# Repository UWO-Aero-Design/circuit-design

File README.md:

# WE Aero Design Onboard Hardware

## Goal
The hardware soloution will contain sensors that allow the team to accurately determine the height and position of the aircraft at any given moment. Also, the system should allow for communication with the ground station through an onboard radio. Logging of in-flight data and accurate GPS information will be necessary. Finally, the system must be able to control 16 individual servos or DC motors.

## Design
Below are screenshots of the current revision of the schematic and board (created in Eagle).

### Schematic

### Board

## Features
#### Radio
[RFM95W](https://www.adafruit.com/product/3072)

#### IMU
[MPU9250](https://www.sparkfun.com/products/13762)

#### Evironment Sensing
[MPL3115A2](https://www.adafruit.com/product/1893)

#### GPS
[Adafruit Ultimate GPS Breakout](https://www.adafruit.com/product/746?gclid=CjwKCAjwscDpBRBnEiwAnQ0HQNEhq5xu14W7TX12W0gVZqHBnbDJNApMf9mEeb73NOOZy2kR0mpCVRoCgI8QAvD_BwE)

#### Battery Monitoring
[INA219](https://www.adafruit.com/product/904)

#### Servo Driver
[PCA9686](https://cdn-shop.adafruit.com/datasheets/PCA9685.pdf)

#### Power
[L7805 and L7806](https://www.mouser.ca/datasheet/2/389/l78m-974157.pdf)

## TODO
- [x] Select parts
- [x] Create schematic
- [x] Layout board
- [x] Route board
- [ ] Order board
- [ ] Test board

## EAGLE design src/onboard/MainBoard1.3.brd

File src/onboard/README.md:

# WE Aero Design Onboard Hardware

## Goal
The hardware soloution will contain sensors that allow the team to accurately determine the height and position of the aircraft at any given moment. Also, the system should allow for communication with the ground station through an onboard radio. Logging of in-flight data and accurate GPS information will be necessary. Finally, the system must be able to control 16 individual servos or DC motors.

## Design
Below are screenshots of the current revision of the schematic and board (created in Eagle).

### Schematic

### Board

## Features
#### Radio
[RFM95W](https://www.adafruit.com/product/3072)

#### IMU
[MPU9250](https://www.sparkfun.com/products/13762)

#### Evironment Sensing
[MPL3115A2](https://www.adafruit.com/product/1893)

#### GPS
[Adafruit Ultimate GPS Breakout](https://www.adafruit.com/product/746?gclid=CjwKCAjwscDpBRBnEiwAnQ0HQNEhq5xu14W7TX12W0gVZqHBnbDJNApMf9mEeb73NOOZy2kR0mpCVRoCgI8QAvD_BwE)

#### Servo Driver
[PCA9686](https://cdn-shop.adafruit.com/datasheets/PCA9685.pdf)

#### Power
[L7805 and L7806](https://www.mouser.ca/datasheet/2/389/l78m-974157.pdf)

## TODO
- [x] Select parts
- [x] Create schematic
- [x] Layout board
- [x] Route board
- [x] Order board
- [ ] Test board

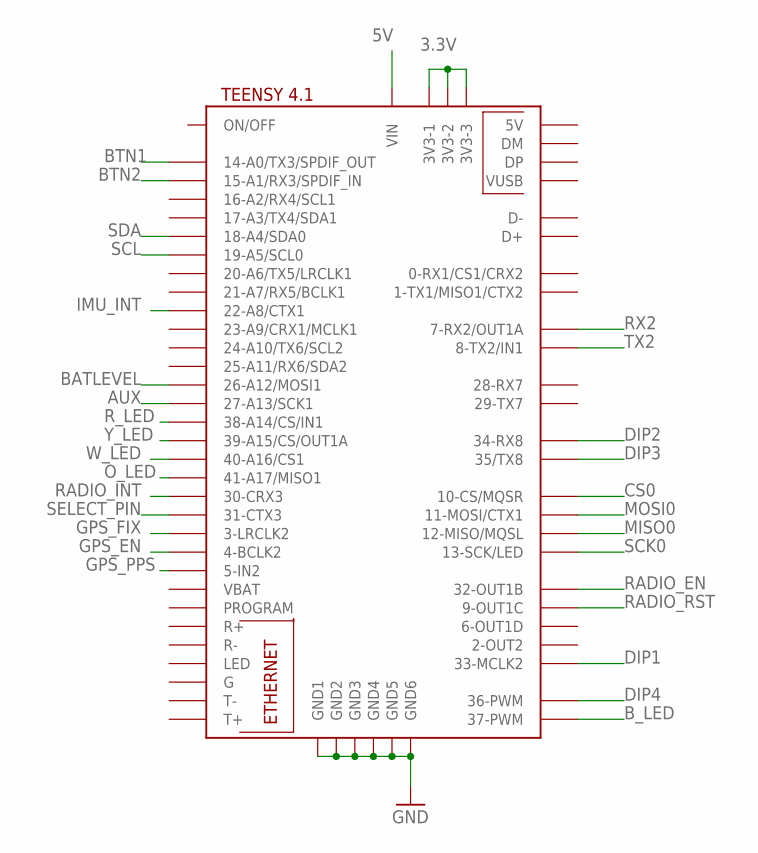
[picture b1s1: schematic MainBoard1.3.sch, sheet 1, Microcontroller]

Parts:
TEENSY4.1: TEENSY41

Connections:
3.3V: TEENSY4.1.3V3-1, TEENSY4.1.3V3-2, TEENSY4.1.3V3-3; also elsewhere on the board
5V: TEENSY4.1.VIN; also elsewhere on the board
AUX: TEENSY4.1.27-A13/SCK1; also elsewhere on the board
BATLEVEL: TEENSY4.1.26-A12/MOSI1; also elsewhere on the board
BTN1: TEENSY4.1.14-A0/TX3/SPDIF_OUT; also elsewhere on the board
BTN2: TEENSY4.1.15-A1/RX3/SPDIF_IN; also elsewhere on the board
B_LED: TEENSY4.1.37-PWM; also elsewhere on the board
CS0: TEENSY4.1.10-CS\MQSR (10-CS/MQSR); also elsewhere on the board
DIP1: TEENSY4.1.33-MCLK2; also elsewhere on the board
DIP2: TEENSY4.1.34-RX8; also elsewhere on the board
DIP3: TEENSY4.1.35-TX8 (35/TX8); also elsewhere on the board
DIP4: TEENSY4.1.36-PWM; also elsewhere on the board
GND: TEENSY4.1.GND1, TEENSY4.1.GND2, TEENSY4.1.GND3, TEENSY4.1.GND4, TEENSY4.1.GND5, TEENSY4.1.GND6; also elsewhere on the board
GPS_EN: TEENSY4.1.4-BCLK2; also elsewhere on the board
GPS_FIX: TEENSY4.1.3-LRCLK2; also elsewhere on the board
GPS_PPS: TEENSY4.1.5-IN2; also elsewhere on the board
IMU_INT: TEENSY4.1.22-A8/CTX1; also elsewhere on the board
MISO0: TEENSY4.1.12-MISO/MQSL; also elsewhere on the board
MOSI0: TEENSY4.1.11-MOSI/CTX1; also elsewhere on the board
O_LED: TEENSY4.1.41-A17/MISO1; also elsewhere on the board
RADIO_EN: TEENSY4.1.32-OUT1B; also elsewhere on the board
RADIO_INT: TEENSY4.1.30-CRX3; also elsewhere on the board
RADIO_RST: TEENSY4.1.9-OUT1C; also elsewhere on the board
RX2: TEENSY4.1.7-RX2/OUT1A; also elsewhere on the board
R_LED: TEENSY4.1.38-A14/CS/IN1; also elsewhere on the board
SCK0: TEENSY4.1.13-SCK/LED; also elsewhere on the board
SCL: TEENSY4.1.19-A5/SCL0; also elsewhere on the board
SDA: TEENSY4.1.18-A4/SDA0; also elsewhere on the board
SELECT_PIN: TEENSY4.1.31-CTX3; also elsewhere on the board
TX2: TEENSY4.1.8-TX2/IN1; also elsewhere on the board
W_LED: TEENSY4.1.40-A16/CS1; also elsewhere on the board
Y_LED: TEENSY4.1.39-A15/CS/OUT1A; also elsewhere on the board

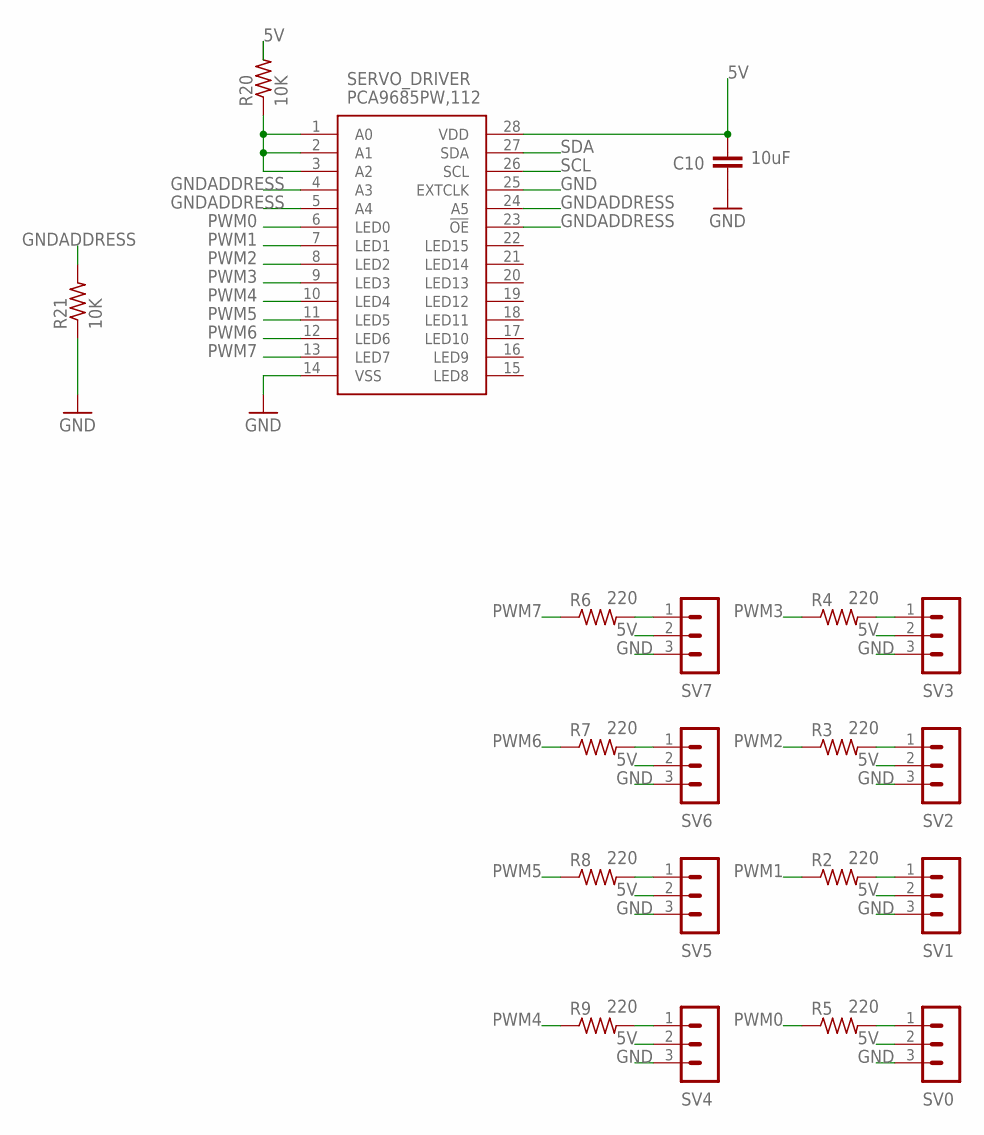
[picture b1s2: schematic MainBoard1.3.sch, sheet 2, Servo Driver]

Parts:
C10: 10uF; C2.5-3
R2, R3, R4, R5, R6, R7, R8, R9: 220; 0204/7
R20, R21: 10K; 0204/7
SERVO_DRIVER: PCA9685PW,112; SOP65P640X110-28N
SV0, SV1, SV2, SV3, SV4, SV5, SV6, SV7: MA03-1

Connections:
5V: C10.1, R20.2, SERVO_DRIVER.28 (VDD), SV0.2, SV1.2, SV2.2, SV3.2, SV4.2, SV5.2, SV6.2, SV7.2; also elsewhere on the board
GND: C10.2, R21.1, SERVO_DRIVER.14 (VSS), SERVO_DRIVER.25 (EXTCLK), SV0.3, SV1.3, SV2.3, SV3.3, SV4.3, SV5.3, SV6.3, SV7.3; also elsewhere on the board
GNDADDRESS: R21.2, SERVO_DRIVER.4 (A3), SERVO_DRIVER.5 (A4), SERVO_DRIVER.23 (!OE), SERVO_DRIVER.24 (A5)
unnamed: R20.1, SERVO_DRIVER.1 (A0), SERVO_DRIVER.2 (A1), SERVO_DRIVER.3 (A2)
unnamed: R6.2, SV7.1
unnamed: R4.2, SV3.1
unnamed: R3.2, SV2.1
unnamed: R7.2, SV6.1
unnamed: R2.2, SV1.1
unnamed: R5.2, SV0.1
unnamed: R9.2, SV4.1
unnamed: R8.2, SV5.1
PWM0: R5.1, SERVO_DRIVER.6 (LED0)
PWM1: R2.1, SERVO_DRIVER.7 (LED1)
PWM2: R3.1, SERVO_DRIVER.8 (LED2)
PWM3: R4.1, SERVO_DRIVER.9 (LED3)
PWM4: R9.1, SERVO_DRIVER.10 (LED4)
PWM5: R8.1, SERVO_DRIVER.11 (LED5)
PWM6: R7.1, SERVO_DRIVER.12 (LED6)
PWM7: R6.1, SERVO_DRIVER.13 (LED7)
SCL: SERVO_DRIVER.26 (SCL); also elsewhere on the board
SDA: SERVO_DRIVER.27 (SDA); also elsewhere on the board

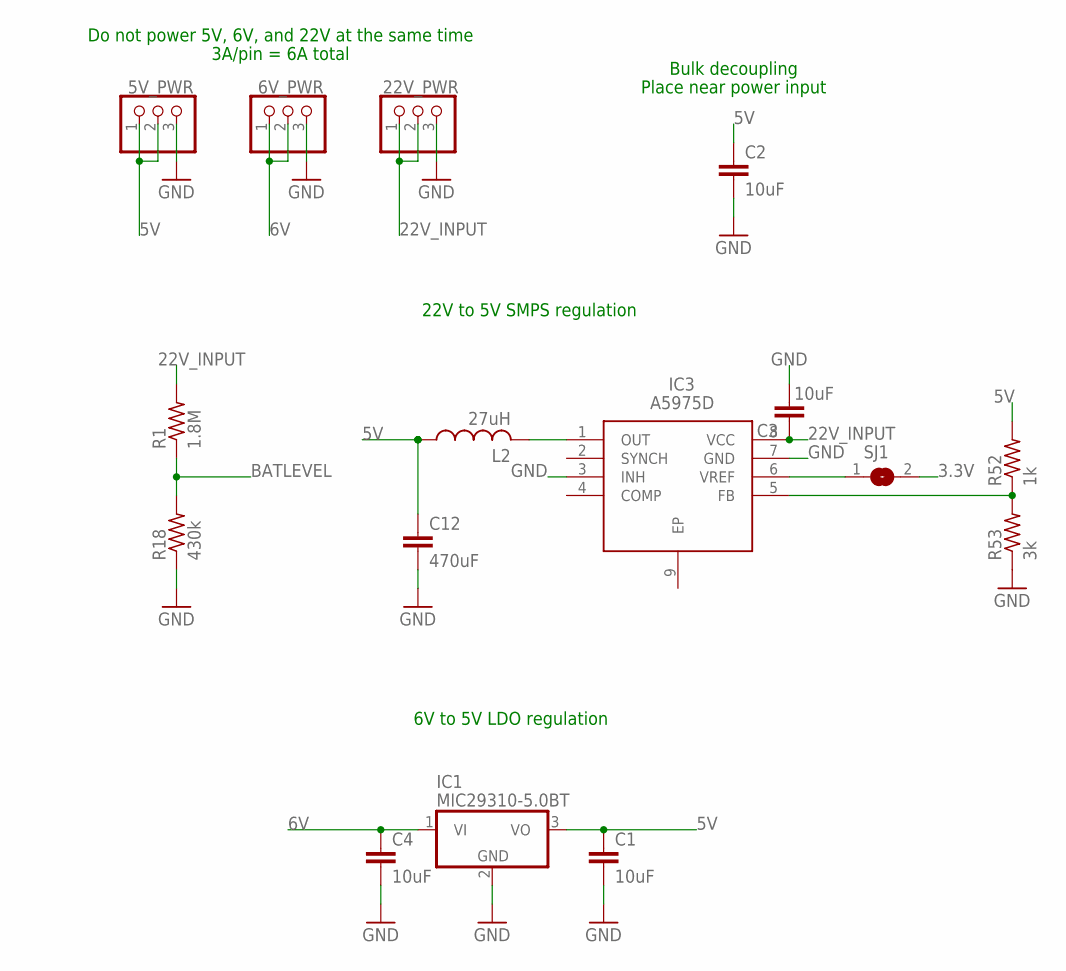
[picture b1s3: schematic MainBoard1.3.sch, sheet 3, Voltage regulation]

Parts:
5V_PWR: 5V_PWR; 1X03
6V_PWR: 6V_PWR; 1X03
22V_PWR: 22V_PWR; 1X03
C1, C2, C3, C4: 10uF; C2.5-3
C12: 470uF; C2.5-3
IC1: MIC29310-5.0BT; TO220V
IC3: A5975D; SOIC127P600X170-9N
L2: 27uH; TFI0307
R1: 1.8M; 0204/7
R18: 430k; 0204/7
R52: 1k; 0204/7
R53: 3k; 0204/7
SJ1: SJ

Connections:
3.3V: SJ1.2; also elsewhere on the board
5V: 5V_PWR.1, 5V_PWR.2, C1.1, C2.1, C12.1, IC1.3 (VO), L2.1, R52.2; also elsewhere on the board
6V: 6V_PWR.1, 6V_PWR.2, C4.1, IC1.1 (VI); also elsewhere on the board
22V_INPUT: 22V_PWR.1, 22V_PWR.2, C3.1, IC3.8 (VCC), R1.2; also elsewhere on the board
BATLEVEL: R1.1, R18.2; also elsewhere on the board
GND: 5V_PWR.3, 6V_PWR.3, 22V_PWR.3, C1.2, C2.2, C3.2, C4.2, C12.2, IC1.2 (GND), IC3.3 (INH), IC3.7 (GND), R18.1, R53.1; also elsewhere on the board
unnamed: IC3.6 (VREF), SJ1.1
unnamed: IC3.1 (OUT), L2.2
unnamed: IC3.5 (FB), R52.1, R53.2

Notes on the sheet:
Do not power 5V, 6V, and 22V at the same time
3A/pin = 6A total
22V to 5V SMPS regulation
6V to 5V LDO regulation
Bulk decoupling
Place near power input

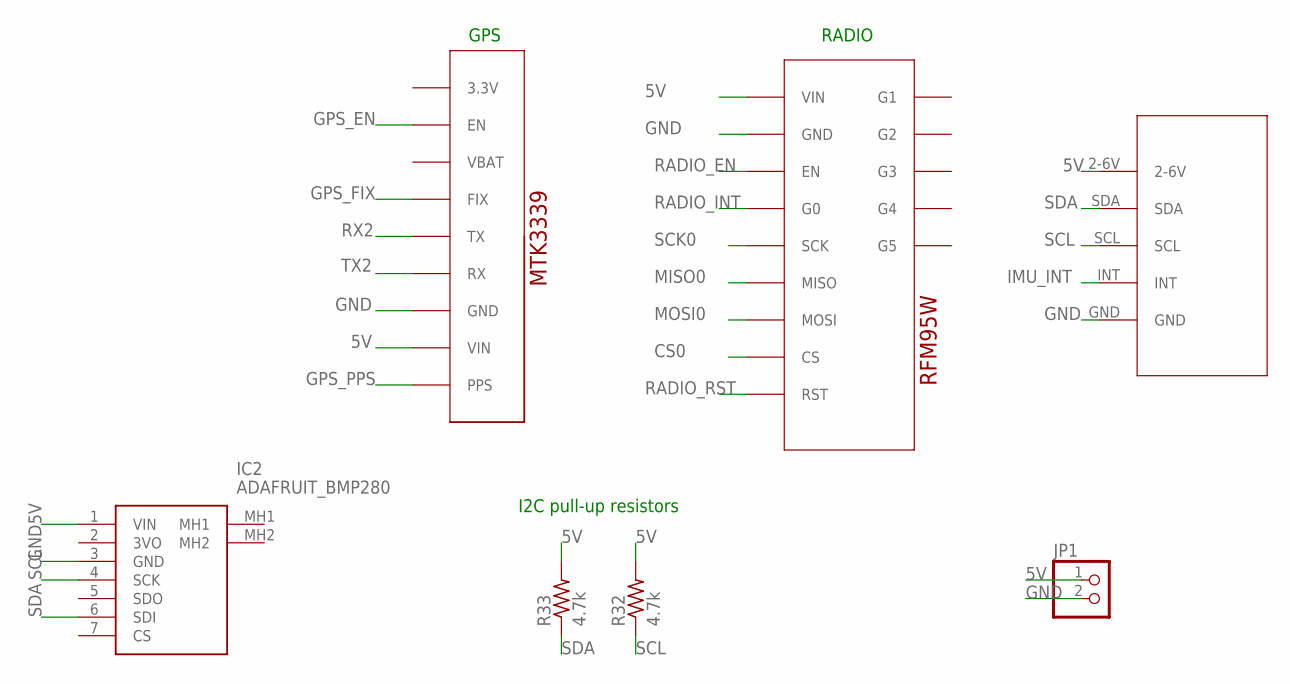
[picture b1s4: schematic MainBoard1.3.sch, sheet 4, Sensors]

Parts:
GPSMTK3339: ADAFRUIT_MTK3339_GPS
IC2: ADAFRUIT_BMP280; ADAFRUITBMP280
IMU: ICM20948BREAKOUTDEVICE; ICM20948BREAKOUT
JP1: PINHD-1X2; 1X02
R32, R33: 4.7k; 0204/7
RADIO: ADAFRUIT_RFM95W_LORA_RADIO

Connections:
5V: GPSMTK3339.VIN, IC2.1 (VIN), IMU.2-6V, JP1.1, R32.2, R33.2, RADIO.1 (VIN); also elsewhere on the board
CS0: RADIO.8 (CS); also elsewhere on the board
GND: GPSMTK3339.GND, IC2.3 (GND), IMU.GND, JP1.2, RADIO.2 (GND); also elsewhere on the board
GPS_EN: GPSMTK3339.EN; also elsewhere on the board
GPS_FIX: GPSMTK3339.FIX; also elsewhere on the board
GPS_PPS: GPSMTK3339.PPS; also elsewhere on the board
IMU_INT: IMU.INT; also elsewhere on the board
MISO0: RADIO.6 (MISO); also elsewhere on the board
MOSI0: RADIO.7 (MOSI); also elsewhere on the board
RADIO_EN: RADIO.3 (EN); also elsewhere on the board
RADIO_INT: RADIO.4 (G0); also elsewhere on the board
RADIO_RST: RADIO.9 (RST); also elsewhere on the board
RX2: GPSMTK3339.TX; also elsewhere on the board
SCK0: RADIO.5 (SCK); also elsewhere on the board
SCL: IC2.4 (SCK), IMU.SCL, R32.1; also elsewhere on the board
SDA: IC2.6 (SDI), IMU.SDA, R33.1; also elsewhere on the board
TX2: GPSMTK3339.RX; also elsewhere on the board

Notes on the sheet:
RADIO
GPS
I2C pull-up resistors

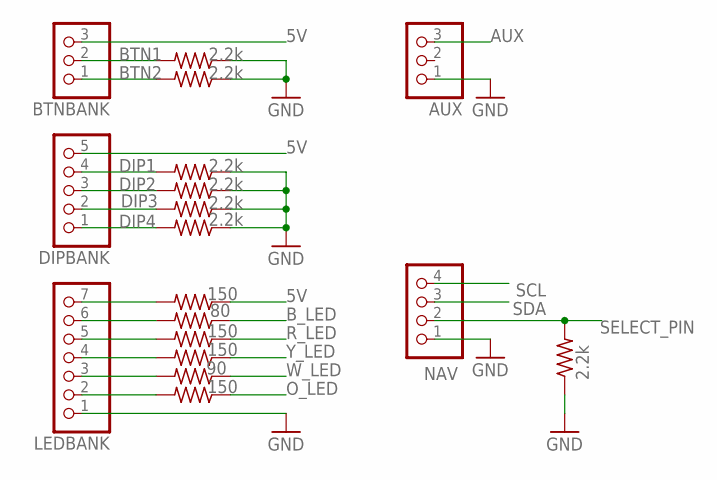
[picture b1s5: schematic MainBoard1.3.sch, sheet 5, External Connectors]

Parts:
AUX: PINHD-1X3; 1X03
BLUE: 80; 0204/7
BTNBANK: PINHD-1X3; 1X03
DIPBANK: PINHD-1X5; 1X05
GREEN: 150; 0204/7
LEDBANK: PINHD-1X7; 1X07
NAV: PINHD-1X4; 1X04
ORANGE: 150; 0204/7
R19, R22, R23, R34, R35, R36, R37: 2.2k; 0204/7
RED: 150; 0204/7
WHITE: 90; 0204/7
YELLOW: 150; 0204/7

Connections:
5V: BTNBANK.3, DIPBANK.5, GREEN.1; also elsewhere on the board
AUX: AUX.3; also elsewhere on the board
BLUE: BLUE.2, LEDBANK.6
BTN1: BTNBANK.2, R19.2; also elsewhere on the board
BTN2: BTNBANK.1, R22.2; also elsewhere on the board
B_LED: BLUE.1; also elsewhere on the board
DIP1: DIPBANK.4, R37.2; also elsewhere on the board
DIP2: DIPBANK.3, R36.2; also elsewhere on the board
DIP3: DIPBANK.2, R34.2; also elsewhere on the board
DIP4: DIPBANK.1, R35.2; also elsewhere on the board
GND: AUX.1, LEDBANK.1, NAV.1, R19.1, R22.1, R23.1, R34.1, R35.1, R36.1, R37.1; also elsewhere on the board
GREEN: GREEN.2, LEDBANK.7
ORANGE: LEDBANK.2, ORANGE.2
O_LED: ORANGE.1; also elsewhere on the board
RED: LEDBANK.5, RED.2
R_LED: RED.1; also elsewhere on the board
SCL: NAV.4; also elsewhere on the board
SDA: NAV.3; also elsewhere on the board
SELECT_PIN: NAV.2, R23.2; also elsewhere on the board
WHITE: LEDBANK.3, WHITE.2
W_LED: WHITE.1; also elsewhere on the board
YELLOW: LEDBANK.4, YELLOW.2
Y_LED: YELLOW.1; also elsewhere on the board

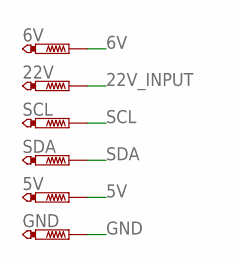
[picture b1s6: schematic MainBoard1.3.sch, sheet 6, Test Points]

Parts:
5V, 6V, 22V: PTR1B1,27; B1,27
GND: PTR1B1,27; B1,27
SCL: PTR1B1,27; B1,27
SDA: PTR1B1,27; B1,27

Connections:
5V: 5V.TP; also elsewhere on the board
6V: 6V.TP; also elsewhere on the board
22V_INPUT: 22V.TP; also elsewhere on the board
GND: GND.TP; also elsewhere on the board
SCL: SCL.TP; also elsewhere on the board
SDA: SDA.TP; also elsewhere on the board

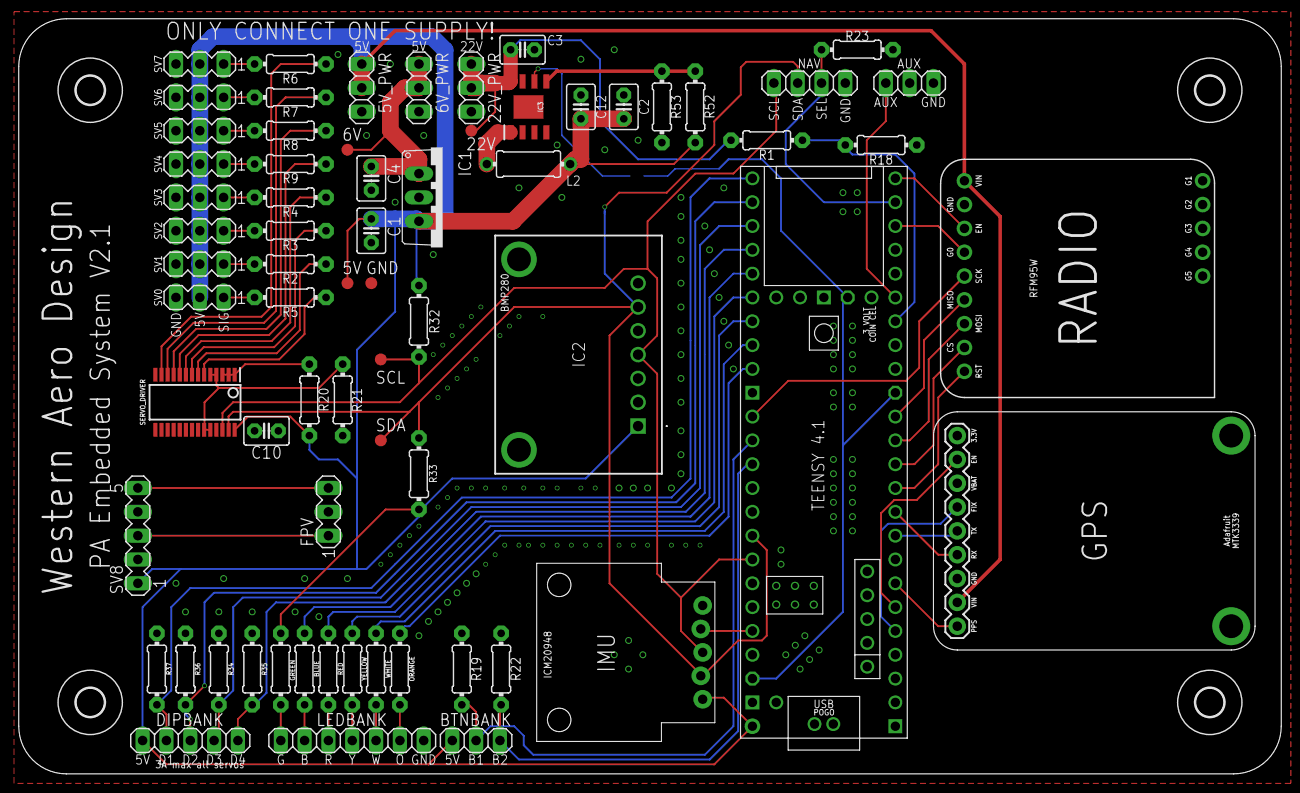
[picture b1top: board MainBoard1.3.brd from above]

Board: 2 copper layers, 134.6 x 80.5 mm, 73 parts (1 on the bottom side), 62 nets.

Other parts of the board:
FPV: MA03-1
SV8: MA05-1
U$1, U$2, U$3, U$4: 3,0

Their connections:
5V: FPV.1, SV8.1, SV8.3; also elsewhere on the board
GND: FPV.2, SV8.2, SV8.4; also elsewhere on the board
VIDEO: FPV.3, SV8.5

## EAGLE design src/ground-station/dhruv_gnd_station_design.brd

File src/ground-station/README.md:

# WE Aero Design Ground Station Utility Hardware

## Goal
The hardware contains a radio and bluetooth module to allow communications between the plane's onboard system and the groundstation web server. It also contains an OLED screen to display basic information to the user as data is sent and recieved.  

## Design
Below are screenshots of the current revision of the schematic and board (created in Eagle).

### Schematic

### Board

## Features
#### Radio
[RFM95W](https://www.adafruit.com/product/3072)

#### Bluetooth
[HC-05](https://components101.com/wireless/hc-05-bluetooth-module)

#### OLED
[128x64 OLED](https://www.adafruit.com/product/326)

## TODO
- [x] Create schematic
- [x] Solder board
- [ ] Test Board

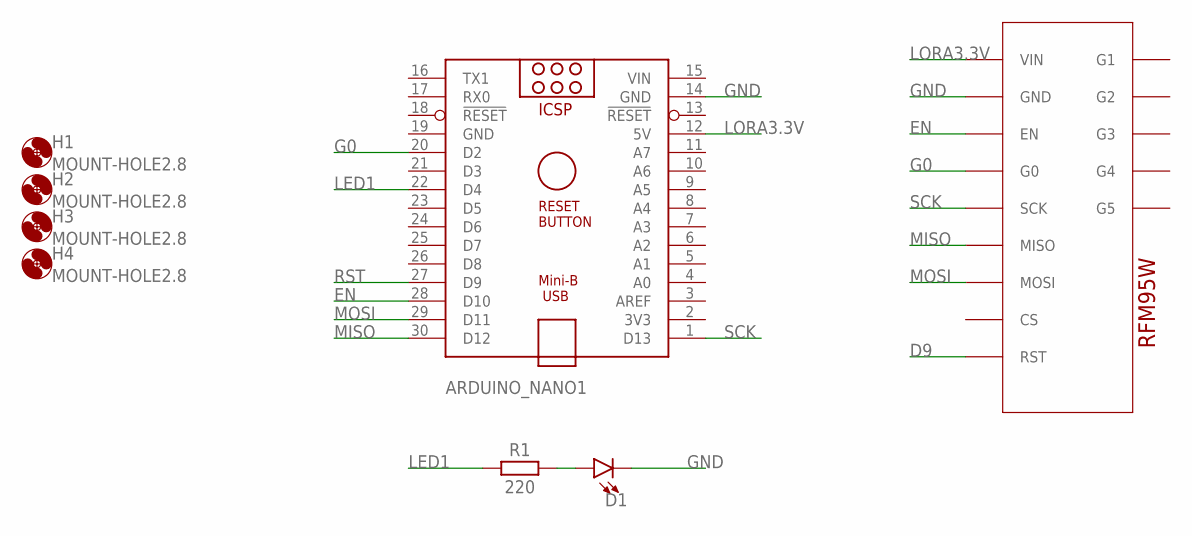
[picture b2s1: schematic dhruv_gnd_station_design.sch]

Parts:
ARDUINO_NANO1: ARDUINO_NANO
D1: LED1206-BOTTOM; LED-1206-BOTTOM
H1, H2, H3, H4: MOUNT-HOLE2.8; 2,8
R1: 220; RESAD724W46L381D178B
U1: ADAFRUIT_RFM95W_LORA_RADIO

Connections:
D9: U1.9 (RST)
EN: ARDUINO_NANO1.28 (D10), U1.3 (EN)
G0: ARDUINO_NANO1.20 (D2), U1.4 (G0)
GND: ARDUINO_NANO1.14 (GND), ARDUINO_NANO1.19 (GND), D1.C, U1.2 (GND)
LED1: ARDUINO_NANO1.22 (D4), R1.1
LORA3.3V: ARDUINO_NANO1.12 (5V), U1.1 (VIN)
MISO: ARDUINO_NANO1.30 (D12), U1.6 (MISO)
MOSI: ARDUINO_NANO1.29 (D11), U1.7 (MOSI)
unnamed: D1.A, R1.2
RST: ARDUINO_NANO1.27 (D9)
SCK: ARDUINO_NANO1.1 (D13), U1.5 (SCK)
VIN: ARDUINO_NANO1.15 (VIN)

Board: 2 copper layers, 8 parts (0 on the bottom side), 9 nets, no tracks yet.

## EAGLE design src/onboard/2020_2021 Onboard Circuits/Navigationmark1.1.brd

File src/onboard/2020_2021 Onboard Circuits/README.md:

# WE Aero Design Onboard Hardware

## Goal
The hardware soloution will contain sensors that allow the team to accurately determine the height and position of the aircraft at any given moment. Also, the system should allow for communication with the ground station through an onboard radio. Logging of in-flight data and accurate GPS information will be necessary. Finally, the system must be able to control 16 individual servos or DC motors.

The team would also like to implement flight stabilization by activating a secondary Teensy which would control four servos attached to control surfaces: 2 aileron, 1 rudder, and 1 elevator. Activation of the secondary Teensy will be done by the Main Teensy. 

## Design
Below are screenshots of the current revision of the schematic and board of the Navigation and Main Teensy (created in Eagle).

### Schematic of Main Teensy

### Board of Main Teensy

### Schematic of Navigation Teensy

### Board of Navigation Teensy

## Features
#### Teensy
[Teensy 4.1](https://www.digikey.ca/en/products/detail/sparkfun-electronics/DEV-16996/13158152)

#### Radio
[RFM95W](https://www.adafruit.com/product/3072)

#### IMU
[ICM20948](https://www.digikey.ca/en/products/detail/pimoroni-ltd/PIM448/10246391)

#### Environment Sensing
[BMP280](https://www.digikey.ca/en/products/detail/adafruit-industries-llc/2651/5604371)

#### Pitot Tube
[Pitot Tube-MPXV7002DP](https://www.digikey.ca/en/products/detail/nxp-usa-inc/MPXV7002DP/1168436)

#### GPS
[Adafruit Ultimate GPS Breakout](https://www.digikey.ca/en/products/detail/adafruit-industries-llc/746/5353613)

#### Servo Driver
[PCA9685PW,112](https://www.digikey.ca/en/products/detail/nxp-usa-inc/PCA9685PW112/2034324)

#### Multiplexer
[CD74AC257M96](https://www.digikey.ca/en/products/detail/texas-instruments/CD74AC257M96/1691832)

#### Power
[A5975D](https://www.digikey.ca/en/products/detail/stmicroelectronics/A5975D/4357599)

## TODO
- [x] Select parts
- [x] Create schematic
- [x] Layout board
- [x] Route board
- [ ] Order board
- [ ] Test board

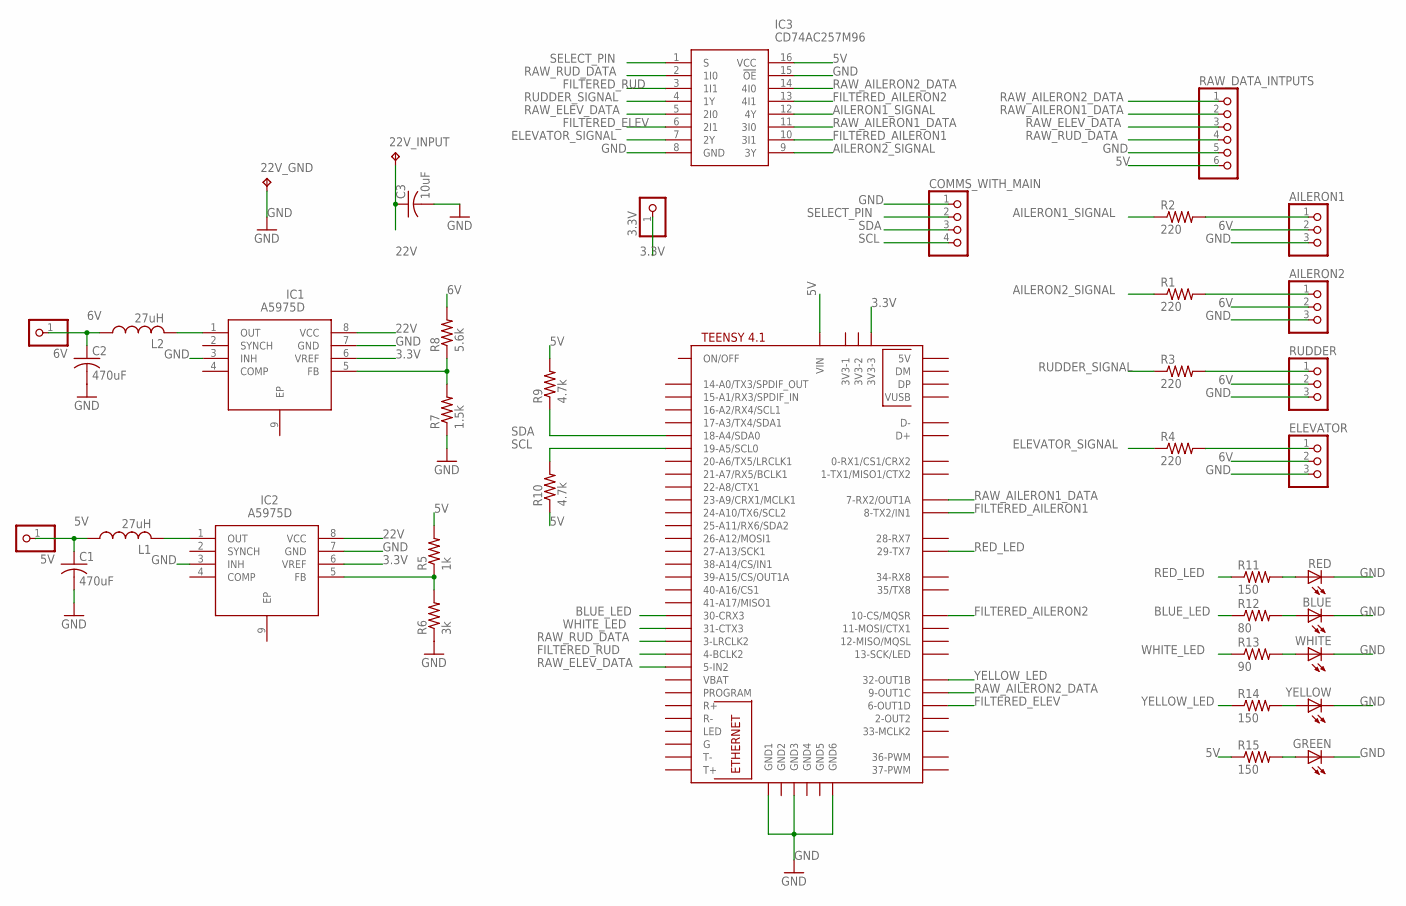
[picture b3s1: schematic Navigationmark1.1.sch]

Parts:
3.3V, 5V, 6V: PINHD-1X1; 1X01
22V_GND, 22V_INPUT: TPPAD1-17Y; P1-17Y
AILERON1, AILERON2: PINHD-1X3; 1X03
BLUE: LED3MM
C1, C2: 470uF; C075-032X103
C3: 10uF; C075-032X103
COMMS_WITH_MAIN: PINHD-1X4; 1X04
ELEVATOR: PINHD-1X3; 1X03
GREEN: LED3MM
IC1, IC2: A5975D; SOIC127P600X170-9N
IC3: CD74AC257M96; SOIC127P600X175-16N
L1, L2: 27uH; 0207/10
R1, R2, R3, R4: 220; 0204/7
R5: 1k; 0204/7
R6: 3k; 0204/7
R7: 1.5k; 0204/7
R8: 5.6k; 0204/7
R9, R10: 4.7k; 0204/7
R11, R14, R15: 150; 0204/7
R12: 80; 0204/7
R13: 90; 0204/7
RAW_DATA_INTPUTS: PINHD-1X6; 1X06
RED: LED3MM
RUDDER: PINHD-1X3; 1X03
U$1: TEENSY41
WHITE: LED3MM
YELLOW: LED3MM

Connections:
3.3V: 3.3V.1, IC1.6 (VREF), IC2.6 (VREF), U$1.3V3-3
5V: 5V.1, C1.1, IC3.16 (VCC), L1.1, R5.2, R9.2, R10.1, R15.1, RAW_DATA_INTPUTS.6, U$1.VIN
6V: 6V.1, AILERON1.2, AILERON2.2, C2.1, ELEVATOR.2, L2.1, R8.2, RUDDER.2
22V: 22V_INPUT.TP, C3.1, IC1.8 (VCC), IC2.8 (VCC)
AILERON1_SIGNAL: IC3.12 (4Y), R2.1
AILERON2_SIGNAL: IC3.9 (3Y), R1.1
BLUE_LED: R12.1, U$1.30-CRX3
ELEVATOR_SIGNAL: IC3.7 (2Y), R4.1
FILTERED_AILERON1: IC3.10 (3I1), U$1.8-TX2/IN1
FILTERED_AILERON2: IC3.13 (4I1), U$1.10-CS\MQSR (10-CS/MQSR)
FILTERED_ELEV: IC3.6 (2I1), U$1.6-OUT1D
FILTERED_RUD: IC3.3 (1I1), U$1.4-BCLK2
GND: 22V_GND.TP, AILERON1.3, AILERON2.3, BLUE.K (C), C1.2, C2.2, C3.2, COMMS_WITH_MAIN.1, ELEVATOR.3, GREEN.K (C), IC1.3 (INH), IC1.7 (GND), IC2.3 (INH), IC2.7 (GND), IC3.8 (GND), IC3.15 (!OE), R6.1, R7.1, RAW_DATA_INTPUTS.5, RED.K (C), RUDDER.3, U$1.GND1, U$1.GND3, U$1.GND6, WHITE.K (C), YELLOW.K (C); also elsewhere on the board
unnamed: AILERON1.1, R2.2
unnamed: GREEN.A, R15.2
unnamed: AILERON2.1, R1.2
unnamed: R3.2, RUDDER.1
unnamed: IC1.1 (OUT), L2.2
unnamed: R11.2, RED.A
unnamed: ELEVATOR.1, R4.2
unnamed: IC2.1 (OUT), L1.2
unnamed: IC2.5 (FB), R5.1, R6.2
unnamed: IC1.5 (FB), R7.2, R8.1
unnamed: BLUE.A, R12.2
unnamed: R13.2, WHITE.A
unnamed: R14.2, YELLOW.A
RAW_AILERON1_DATA: IC3.11 (3I0), RAW_DATA_INTPUTS.2, U$1.7-RX2/OUT1A
RAW_AILERON2_DATA: IC3.14 (4I0), RAW_DATA_INTPUTS.1, U$1.9-OUT1C
RAW_ELEV_DATA: IC3.5 (2I0), RAW_DATA_INTPUTS.3, U$1.5-IN2
RAW_RUD_DATA: IC3.2 (1I0), RAW_DATA_INTPUTS.4, U$1.3-LRCLK2
RED_LED: R11.1, U$1.29-TX7
RUDDER_SIGNAL: IC3.4 (1Y), R3.1
SCL: COMMS_WITH_MAIN.4, R10.2, U$1.19-A5/SCL0; also elsewhere on the board
SDA: COMMS_WITH_MAIN.3, R9.1, U$1.18-A4/SDA0; also elsewhere on the board
SELECT_PIN: COMMS_WITH_MAIN.2, IC3.1 (S); also elsewhere on the board
WHITE_LED: R13.1, U$1.31-CTX3
YELLOW_LED: R14.1, U$1.32-OUT1B

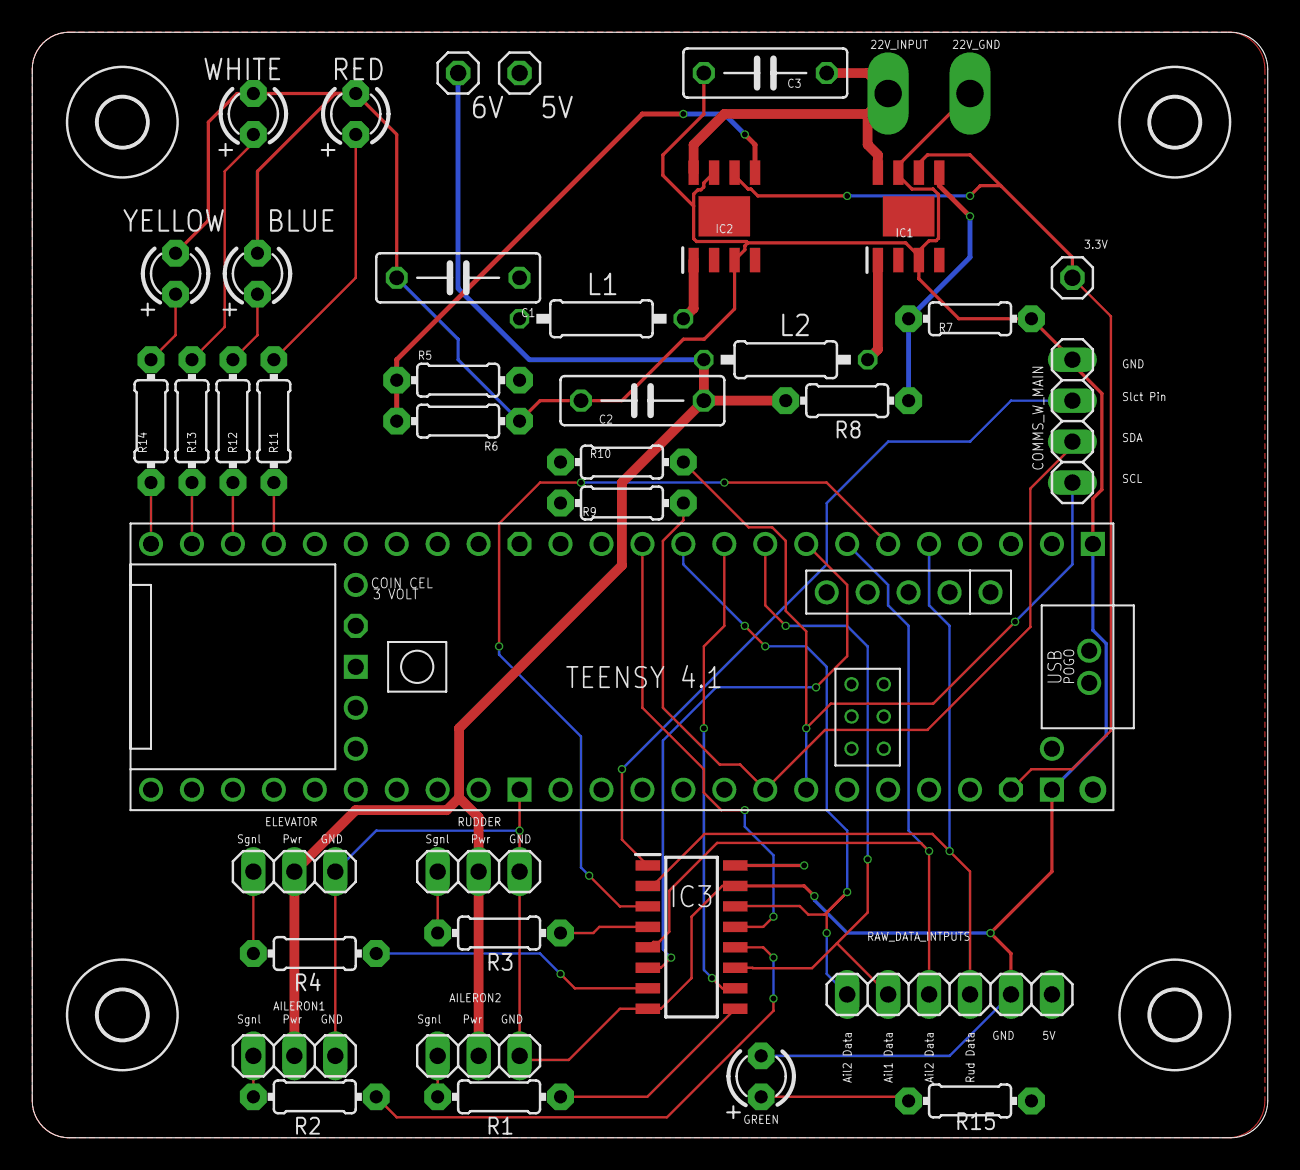
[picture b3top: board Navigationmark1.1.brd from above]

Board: 2 copper layers, 76.6 x 68.6 mm, 44 parts (0 on the bottom side), 37 nets.

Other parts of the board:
COMMS_W_MAIN: 1X04
E$1, E$2, E$3, E$4: 3,0

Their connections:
GND: COMMS_W_MAIN.1; also elsewhere on the board
SCL: COMMS_W_MAIN.4; also elsewhere on the board
SDA: COMMS_W_MAIN.3; also elsewhere on the board
SELECT_PIN: COMMS_W_MAIN.2; also elsewhere on the board

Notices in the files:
parts and their libraries:
SparkFun-Aesthetics: Licensing: Creative Commons ShareAlike 4.0 International - https://creativecommons.org/licenses/by-sa/4.0
microbuilder: This work is placed in the public domain, and may be freely used for commercial and non-commercial work with the following conditions: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
